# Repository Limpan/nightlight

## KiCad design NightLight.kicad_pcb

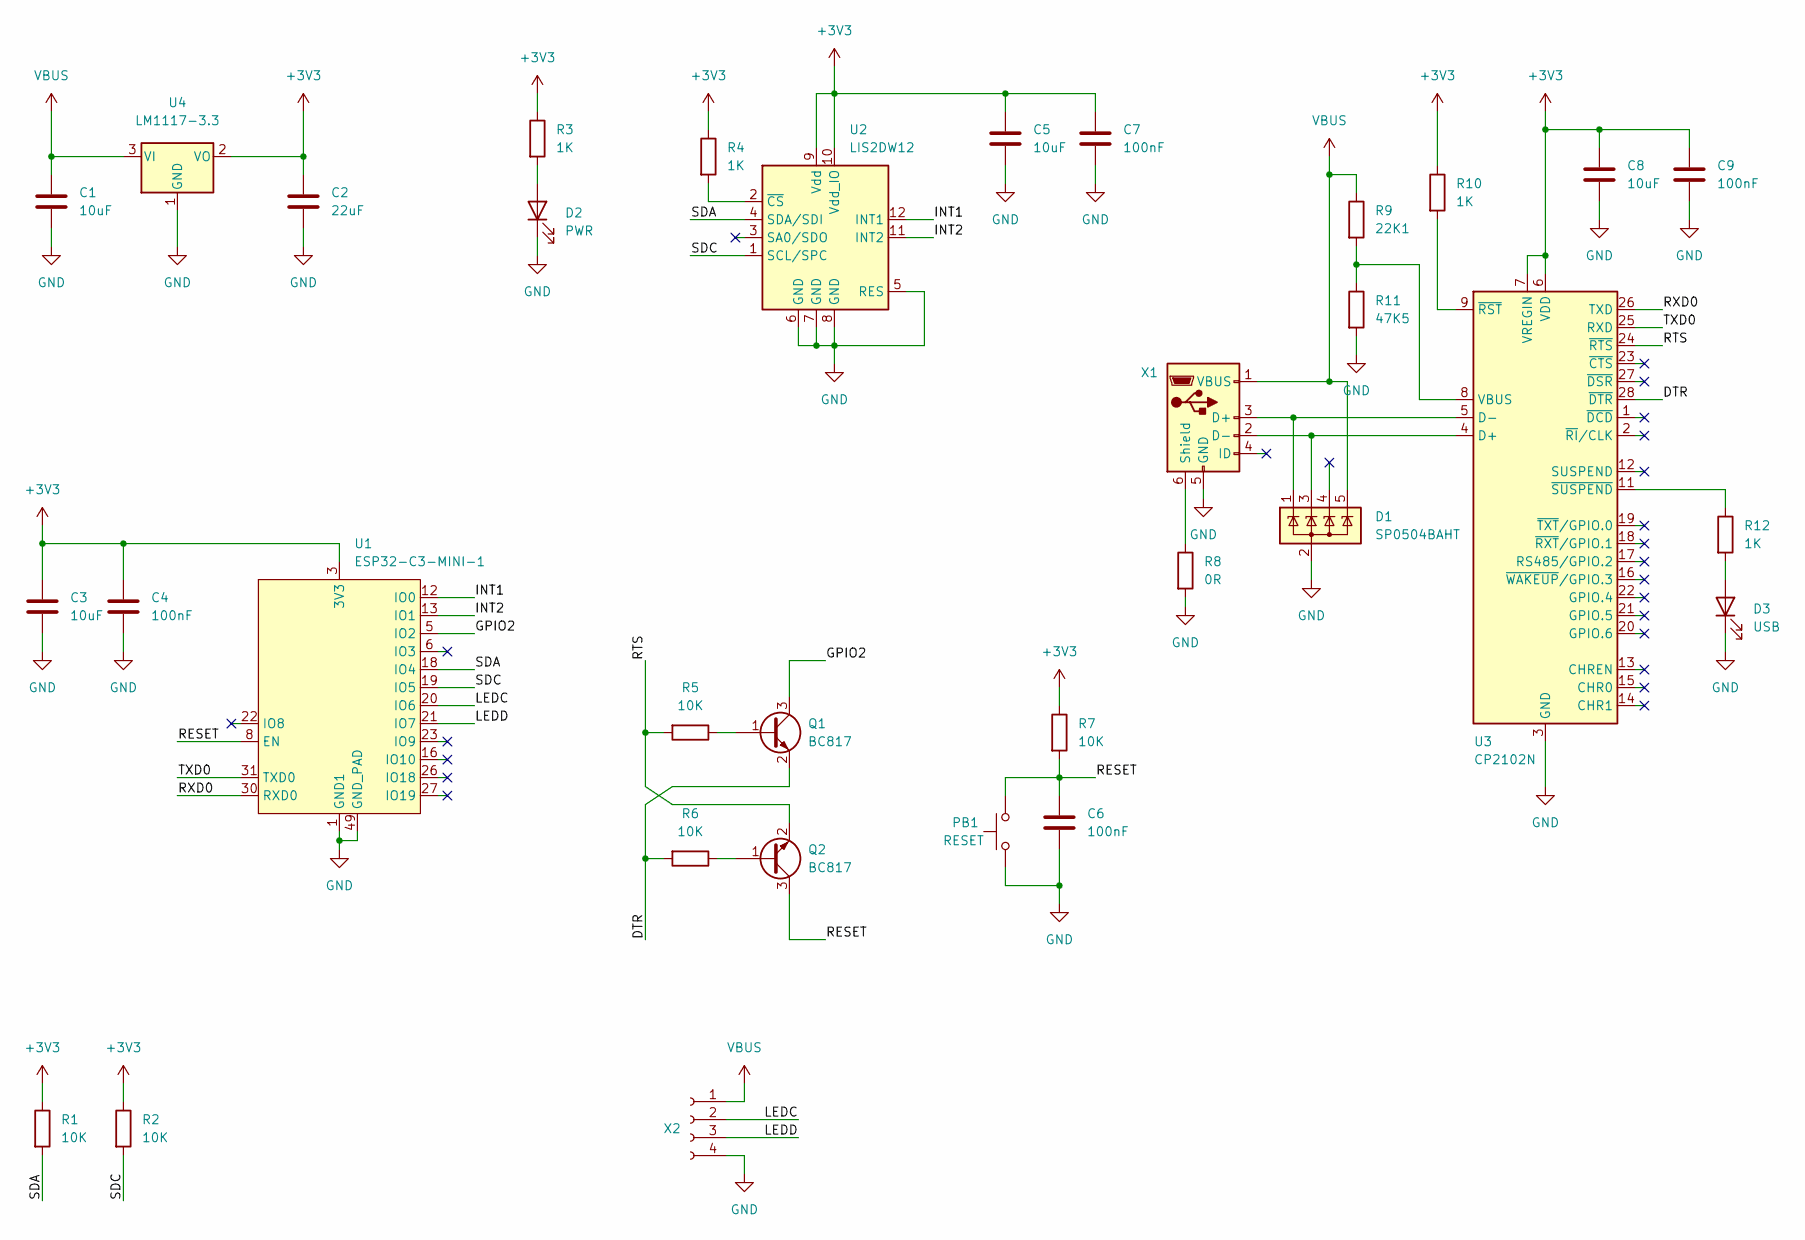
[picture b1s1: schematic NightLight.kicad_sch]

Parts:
C1, C3, C5, C8: 10uF; C_0805_2012Metric_Pad1.18x1.45mm_HandSolder
C2: 22uF; CP_Elec_4x5.4
C4, C6, C7, C9: 100nF; C_0805_2012Metric_Pad1.18x1.45mm_HandSolder
D1: SP0504BAHT; SOT-23-5
D2: PWR; D_0805_2012Metric_Pad1.15x1.40mm_HandSolder
D3: USB; D_0805_2012Metric_Pad1.15x1.40mm_HandSolder
PB1: RESET; KSR Series
Q1, Q2: BC817; SOT-23_Handsoldering
R1, R2, R5, R6, R7: 10K; R_0805_2012Metric_Pad1.20x1.40mm_HandSolder
R3, R4, R10, R12: 1K; R_0805_2012Metric_Pad1.20x1.40mm_HandSolder
R8: 0R; R_0805_2012Metric_Pad1.20x1.40mm_HandSolder
R9: 22K1; R_0805_2012Metric_Pad1.20x1.40mm_HandSolder
R11: 47K5; R_0805_2012Metric_Pad1.20x1.40mm_HandSolder
U1: ESP32-C3-MINI-1
U2: LIS2DW12; LGA-12_2x2mm_P0.5mm
U3: CP2102N; QFN-28-1EP_5x5mm_P0.5mm_EP3.35x3.35mm
U4: LM1117-3.3; SOT-223-3_TabPin2
X1: USB_B_Micro
X2: Conn_01x04_Female; JST_PH_S4B-PH-K_1x04_P2.00mm_Horizontal

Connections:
+3V3: C2.1, C3.1, C4.1, C5.1, C7.1, C8.1, C9.1, R1.1, R2.1, R3.1, R4.1, R7.1, R10.1, U1.3 (3V3), U2.9 (Vdd), U2.10 (Vdd_IO), U3.6 (VDD), U3.7 (VREGIN), U4.2 (VO)
/DTR: Q1.2 (E), R6.2, U3.28 (~DTR)
/GPIO2: Q1.3 (C), U1.5 (IO2)
/INT1: U1.12 (IO0), U2.12 (INT1)
/INT2: U1.13 (IO1), U2.11 (INT2)
/LEDC: U1.20 (IO6), X2.2
/LEDD: U1.21 (IO7), X2.3
/RESET: C6.1, PB1.2, Q2.3 (C), R7.2, U1.8 (EN)
/RTS: Q2.2 (E), R5.2, U3.24 (~RTS)
/RXD0: U1.30 (RXD0), U3.26 (TXD)
/SDA: R1.2, U1.18 (IO4), U2.4 (SDA/SDI)
/SDC: R2.2, U1.19 (IO5), U2.1 (SCL/SPC)
/TXD0: U1.31 (TXD0), U3.25 (RXD)
GND: C1.2, C2.2, C3.2, C4.2, C5.2, C6.2, C7.2, C8.2, C9.2, D1.2 (A), D2.1 (K), D3.1 (K), PB1.1, R8.2, R11.2, U1.1 (GND1), U1.2 (GND2), U1.11 (GND11), U1.14 (GND14), U1.36 (GND36), U1.37 (GND37), U1.38 (GND38), U1.39 (GND39), U1.40 (GND40), U1.41 (GND41), U1.42 (GND42), U1.43 (GND43), U1.44 (GND44), U1.45 (GND45), U1.46 (GND46), U1.47 (GND47), U1.48 (GND48), U1.49 (GND_PAD), U1.50 (GND50), U1.51 (GND51), U1.52 (GND52), U1.53 (GND53), U2.5 (RES), U2.6 (GND), U2.7 (GND), U2.8 (GND), U3.3 (GND), U3.29 (GND), U4.1 (GND), X1.5 (GND), X2.4
unnamed: D1.1 (K), U3.5 (D-), X1.3 (D+)
unnamed: D1.3 (K), U3.4 (D+), X1.2 (D-)
unnamed: D2.2 (A), R3.2
unnamed: D3.2 (A), R12.2
unnamed: Q1.1 (B), R5.1
unnamed: Q2.1 (B), R6.1
unnamed: R4.2, U2.2 (~CS)
unnamed: R8.1, X1.6 (Shield)
unnamed: R10.2, U3.9 (~RST)
unnamed: R9.2, R11.1, U3.8 (VBUS)
unnamed: R12.1, U3.11 (~SUSPEND)
VBUS: C1.1, D1.5 (K), R9.1, U4.3 (VI), X1.1 (VBUS), X2.1

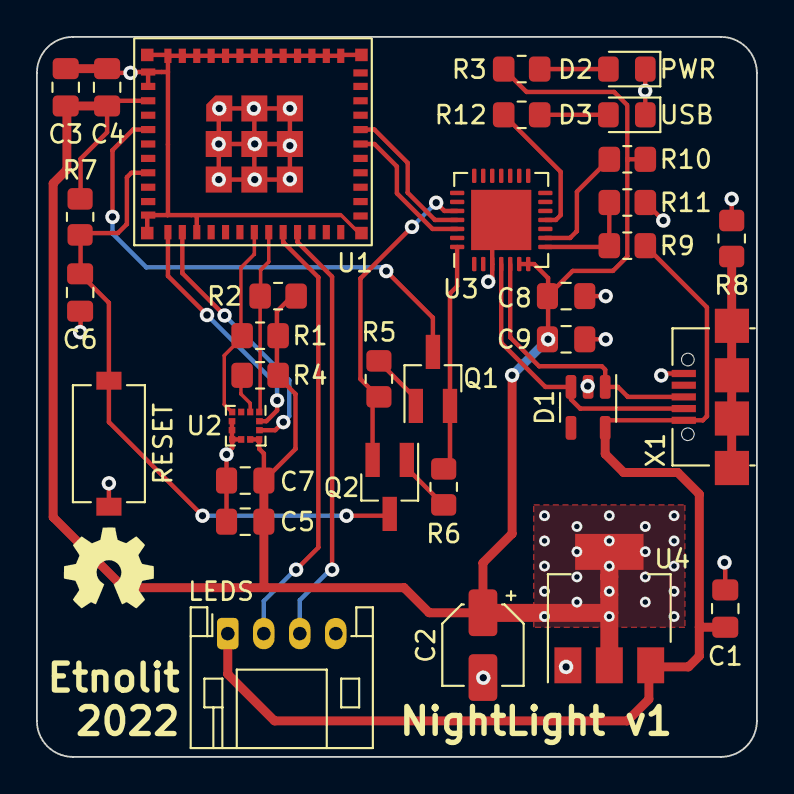
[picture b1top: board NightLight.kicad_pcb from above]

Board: 2 copper layers, 40.0 x 40.0 mm, 33 parts (0 on the bottom side), 26 nets.

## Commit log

2022-01-24 Preliminary component placement on PCB.
2022-01-26 Improved layout.
2022-01-27 Minor improvents and cleanups.
2022-02-13 Final fixes. Ready for fab?
